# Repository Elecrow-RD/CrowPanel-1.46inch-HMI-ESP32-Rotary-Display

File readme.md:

### 1, Product picture

### 2, Product version number

|      | Hardware | Software | Remark |
| ---- | -------- | -------- | ------ |
| 1    | V1.0     | V1.0     | latest |

### 3, product information

#### Display Module Specifications
| Main Chip: ESP32-S3R8  |                                                              |
| ---------------------- | ------------------------------------------------------------ |
| Processor              | Equipped with high-performance Xtensa 32-bit LX7 dual-core processor, with a main frequency of up to 240MHz |
| System memory          | 512KB SRAM、8M PSRAM                                         |
| Storage                | 16M Flash                                                    |
| Screen                 |                                                              |
| Size                   | 1.46 inch                                                    |
| Screen Type            | IPS                                                          |
| Touch Type             | Capacitive Touch                                             |
| Resolution             | 360*360                                                      |
| Wireless Communication |                                                              |
| Bluetooth              | Bluetooth Low Energy and Bluetooth 5.0                       |
| WiFi                   | Support 802.11a/b/g/n，2.4GH                                 |
| Hardware               |                                                              |
| UART Interface         | 2x UART, ZX-MX 1.25-4P                                       |
| I2C interface          | ZX-MX 1.25-4P                                                |
| FPC connector          | 12P, Power supply burning port, Pitch: 0.5 mm.               |
| Button                 | RESET button, BOOT button, confirmation button (knob press switch) |
| LED Light              | Power indicator, LED ambient light                           |
| Other                  |                                                              |
| Power Input            | 5V/1A                                                        |
| Operating temperature  | -20~65℃                                                      |
| Storage temperature    | -40~80℃                                                      |
| Operation Power        | Module：DC5V  Main Chip：3.3V                                |
| Size                   | 60\*60*27.5mm                                                |
| Shell                  | Plastic + acrylic                                            |
| Net Weight             | 60g                                                          |

### 4, Use the driver module

| Name | dependency library |
| ---- | ------------------ |
| LVGL | lvgl/lvgl@8.3.11   |

### 5,Quick Start

##### Arduino IDE starts

1.Download the library files used by this product to the 'libraries' folder.

C:\Users\Documents\Arduino\libraries\

2.Open the Arduino IDE

3.Open the code configuration environment and burn it.

### 6,Folder structure.

|--3D file： Contains 3D model files (.stp) for the hardware. These files can be used for visualization, enclosure design, or integration into CAD software.

|--Datasheet: Includes datasheets for components used in the project, providing detailed specifications, electrical characteristics, and pin configurations.

|--Eagle_SCH&PCB: Contains **Eagle CAD** schematic (`.sch`) and PCB layout (`.brd`) files. These are used for circuit design and PCB manufacturing.

|--example: Provides example code and projects to demonstrate how to use the hardware and libraries. These examples help users get started quickly.

|--factory_firmware: Stores pre-compiled factory firmware that can be directly flashed onto the device. This ensures the device runs the default functionality.

|--factory_sourcecode: Contains the source code for the factory firmware, allowing users to modify and rebuild the firmware as needed.

### 7,Pin definition

| Function       | GPIO   |
| -------------- | ------ |
| LCD SCLK       | GPIO10 |
| LCD MOSI       | GPIO11 |
| LCD CS         | GPIO9  |
| LCD DC         | GPIO3  |
| LCD RST        | GPIO14 |
| Touch SDA      | GPIO6  |
| Touch SCL      | GPIO7  |
| Touch INT      | GPIO5  |
| Touch RST      | GPIO13 |
| Backlight      | GPIO46 |
| Encoder A      | GPIO45 |
| Encoder B      | GPIO42 |
| Encoder Switch | GPIO41 |
| Power LED      | GPIO40 |
| RGB LED        | GPIO48 |
| I2C_SDA        | GPIO38 |
| I2C_SCL        | GPIO39 |

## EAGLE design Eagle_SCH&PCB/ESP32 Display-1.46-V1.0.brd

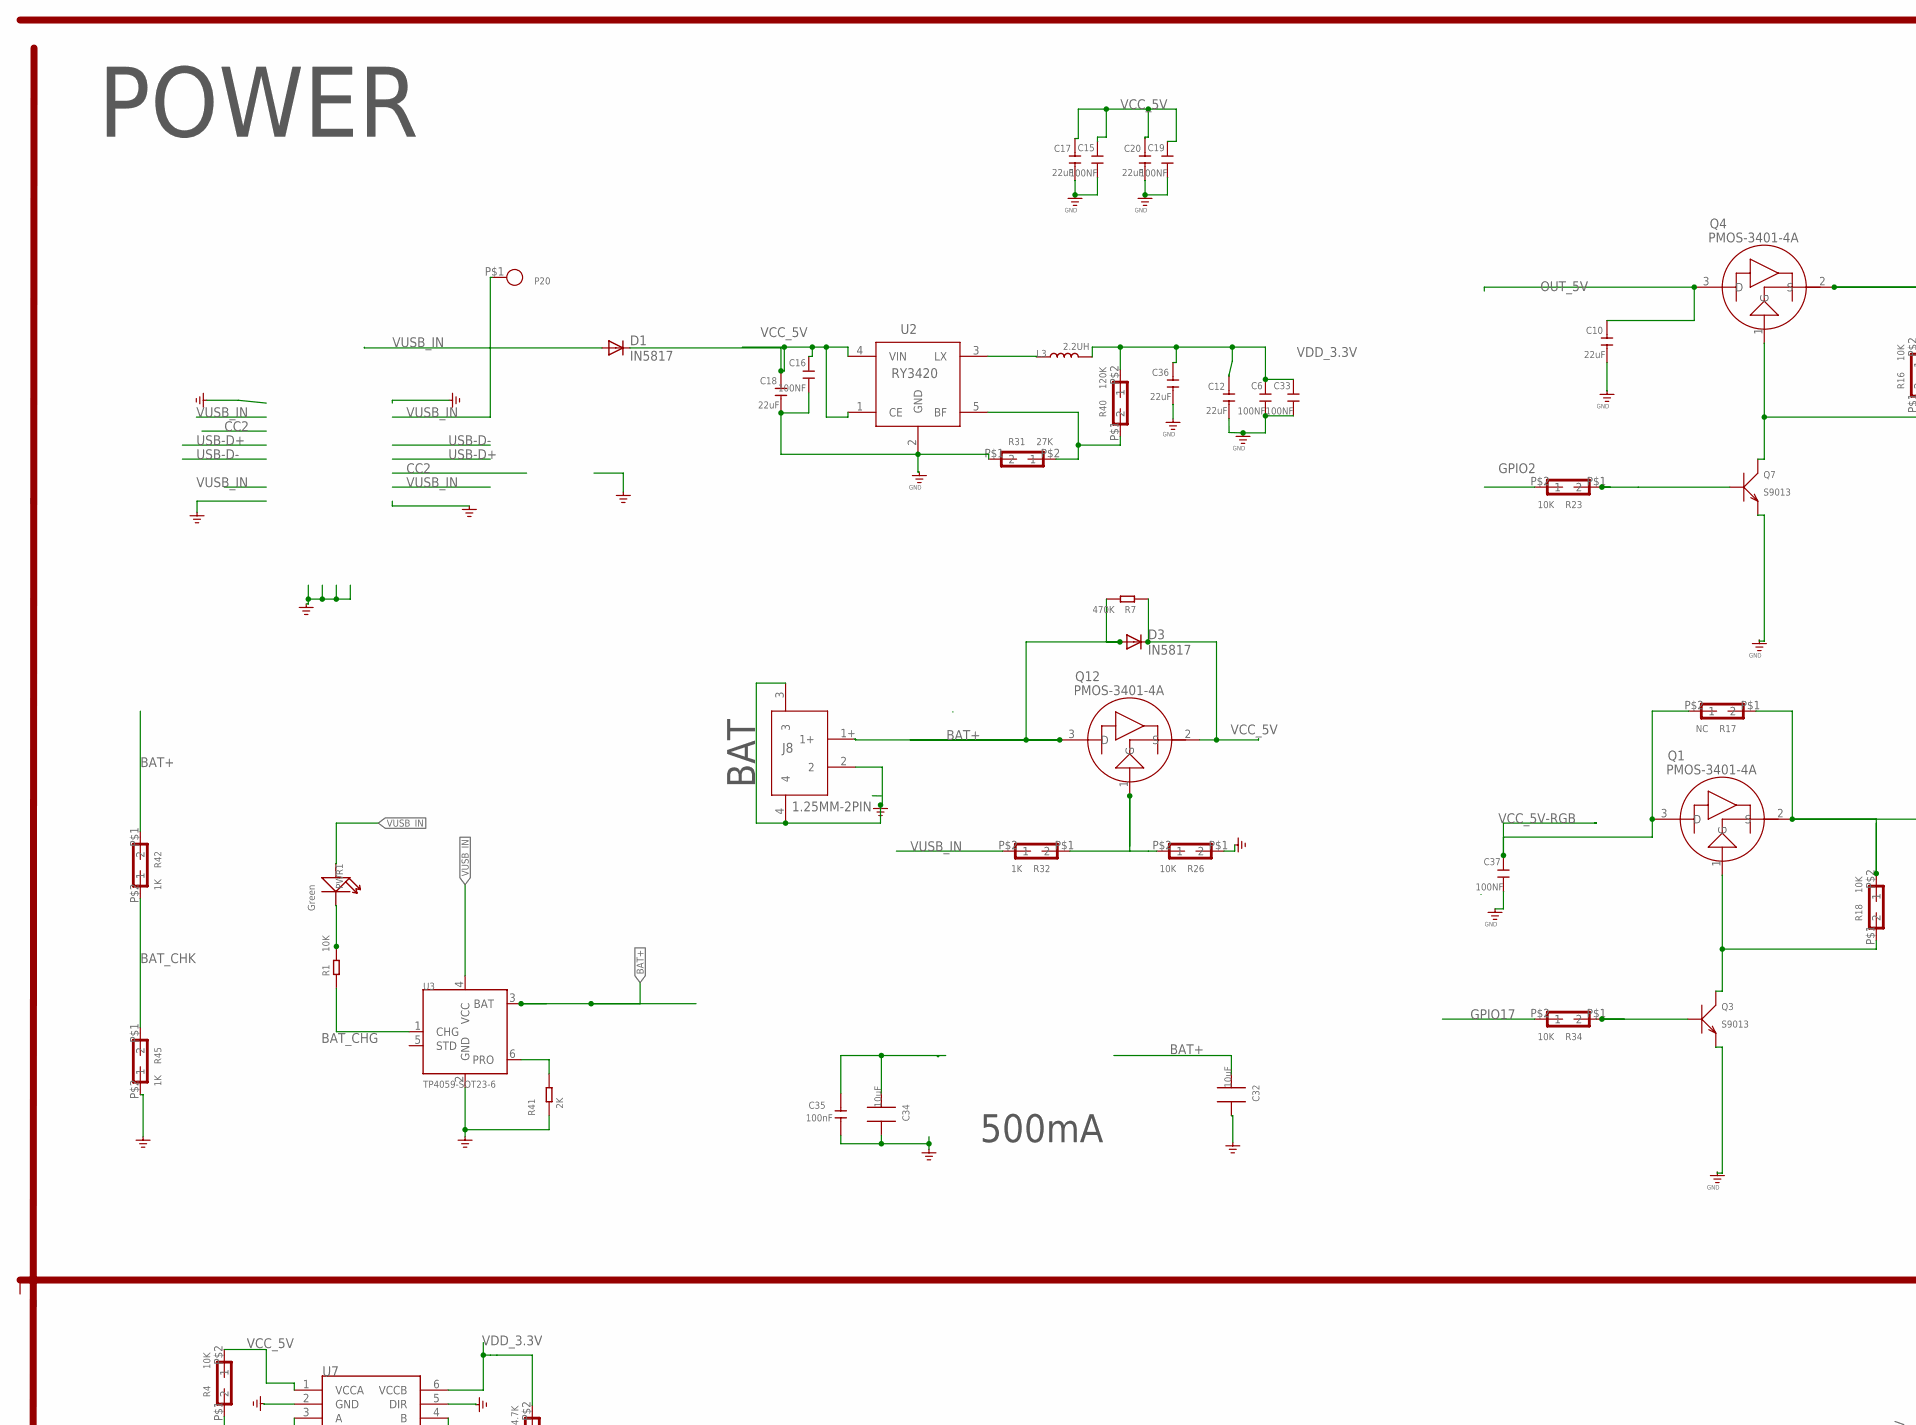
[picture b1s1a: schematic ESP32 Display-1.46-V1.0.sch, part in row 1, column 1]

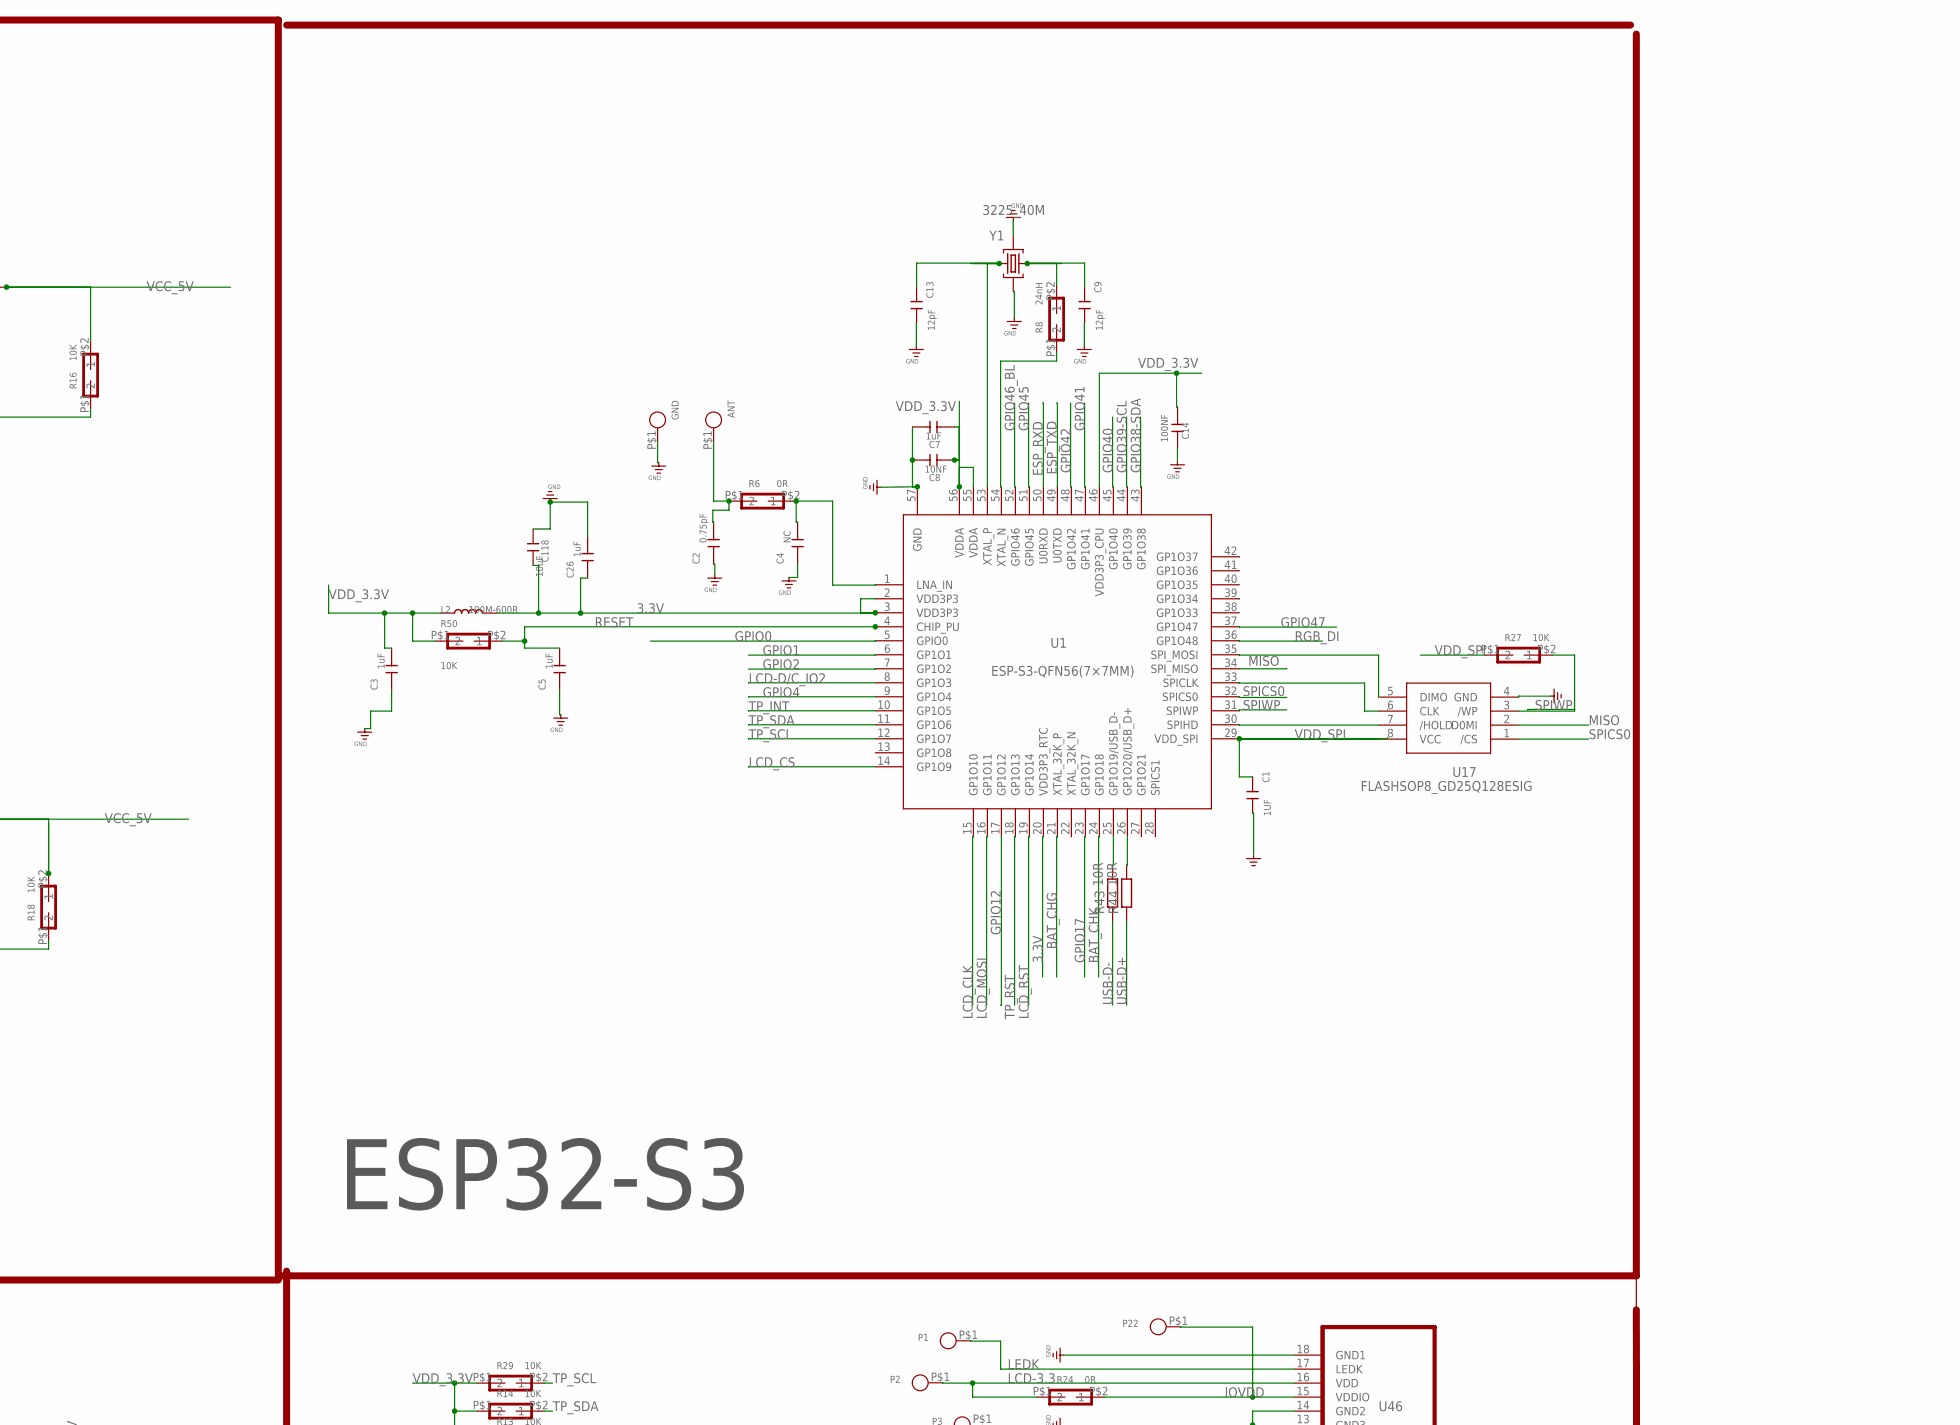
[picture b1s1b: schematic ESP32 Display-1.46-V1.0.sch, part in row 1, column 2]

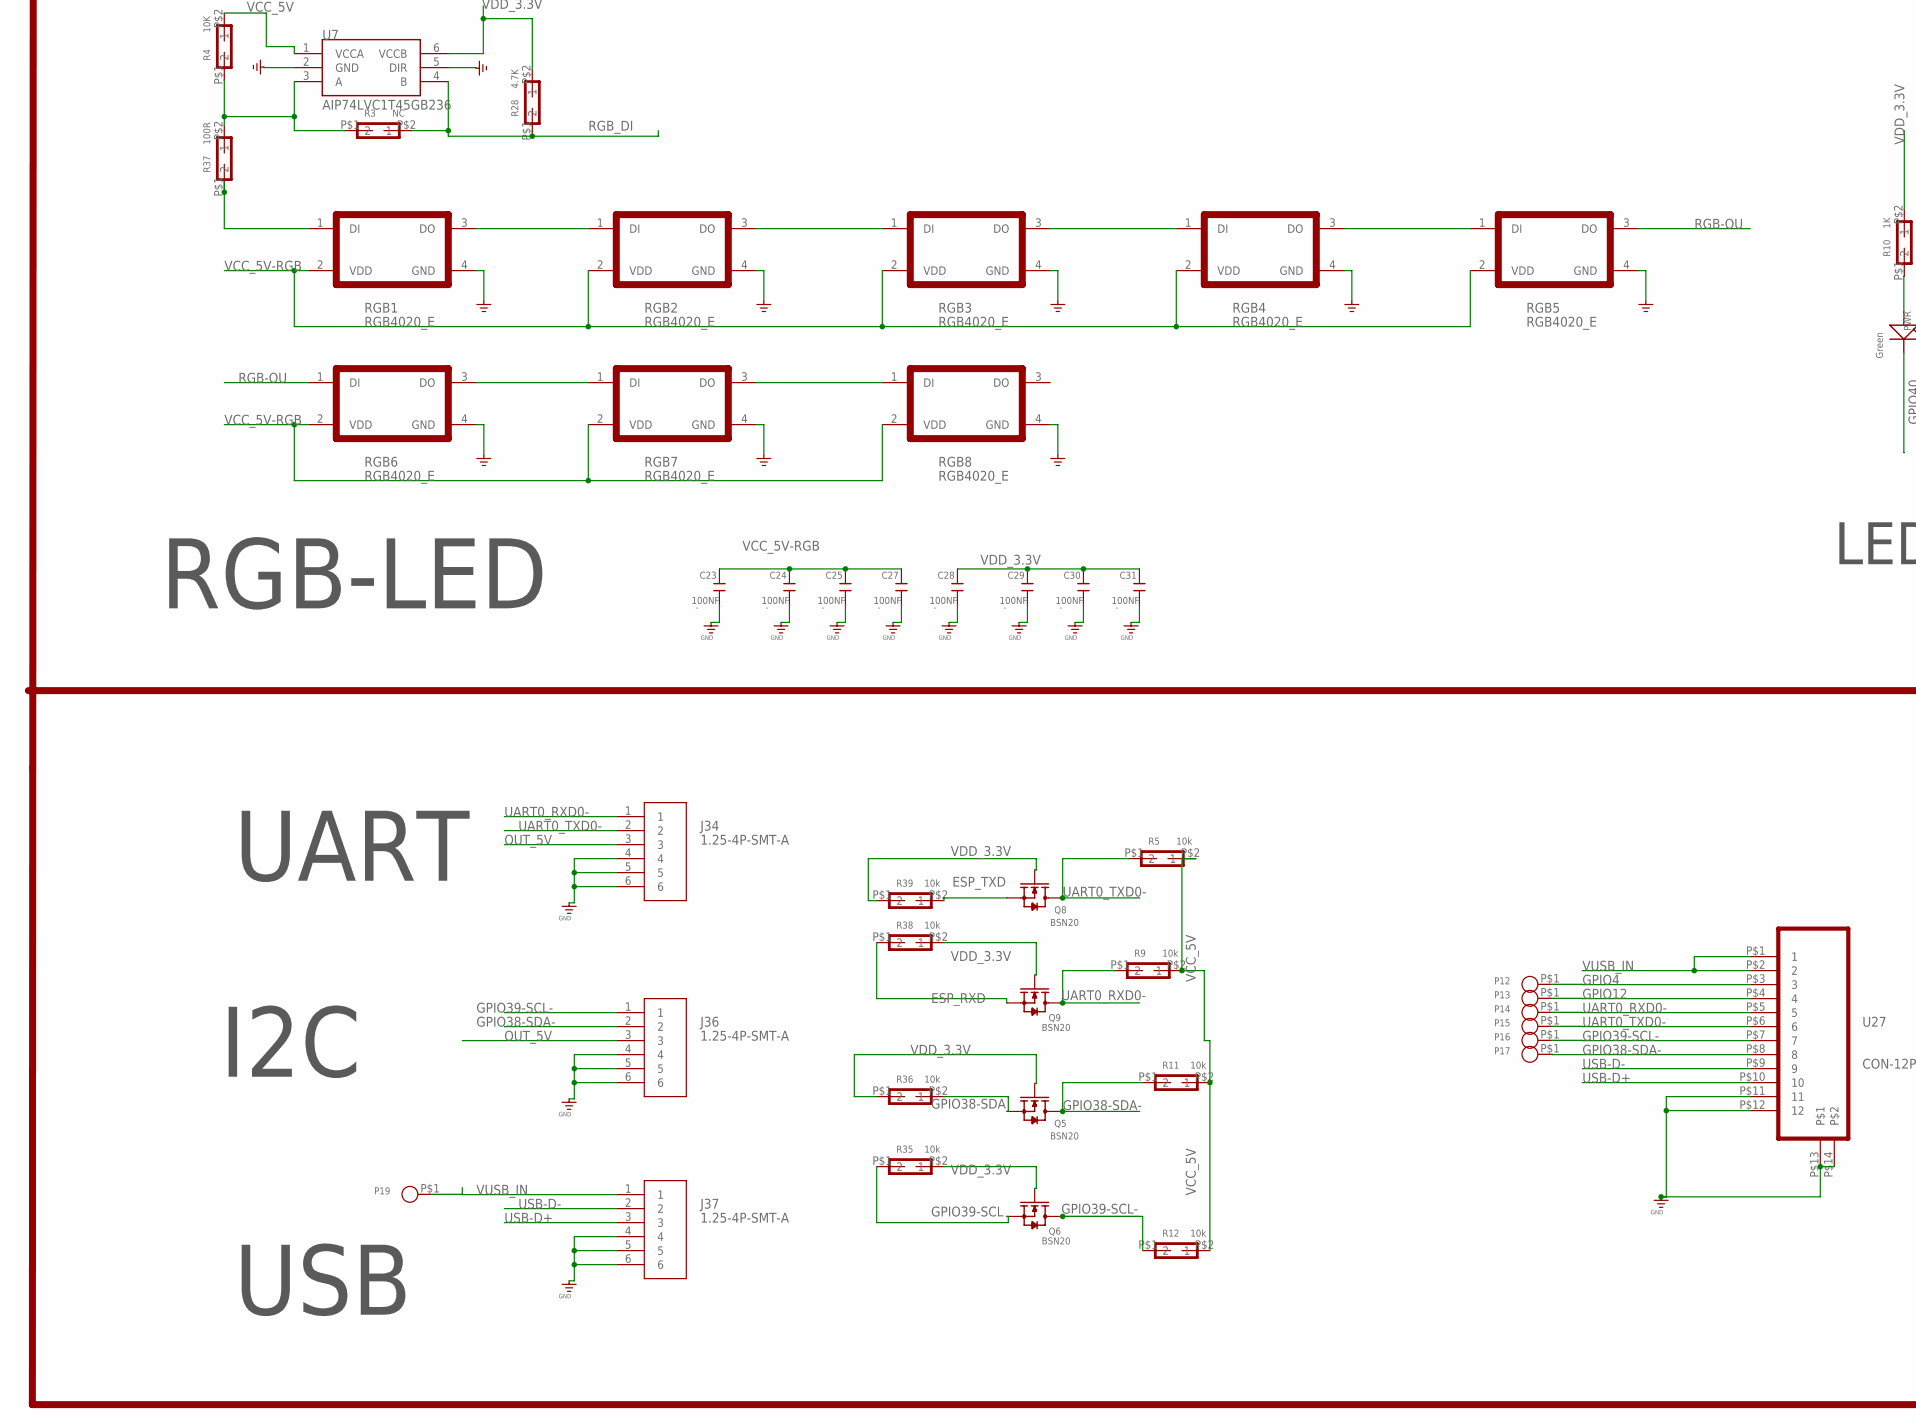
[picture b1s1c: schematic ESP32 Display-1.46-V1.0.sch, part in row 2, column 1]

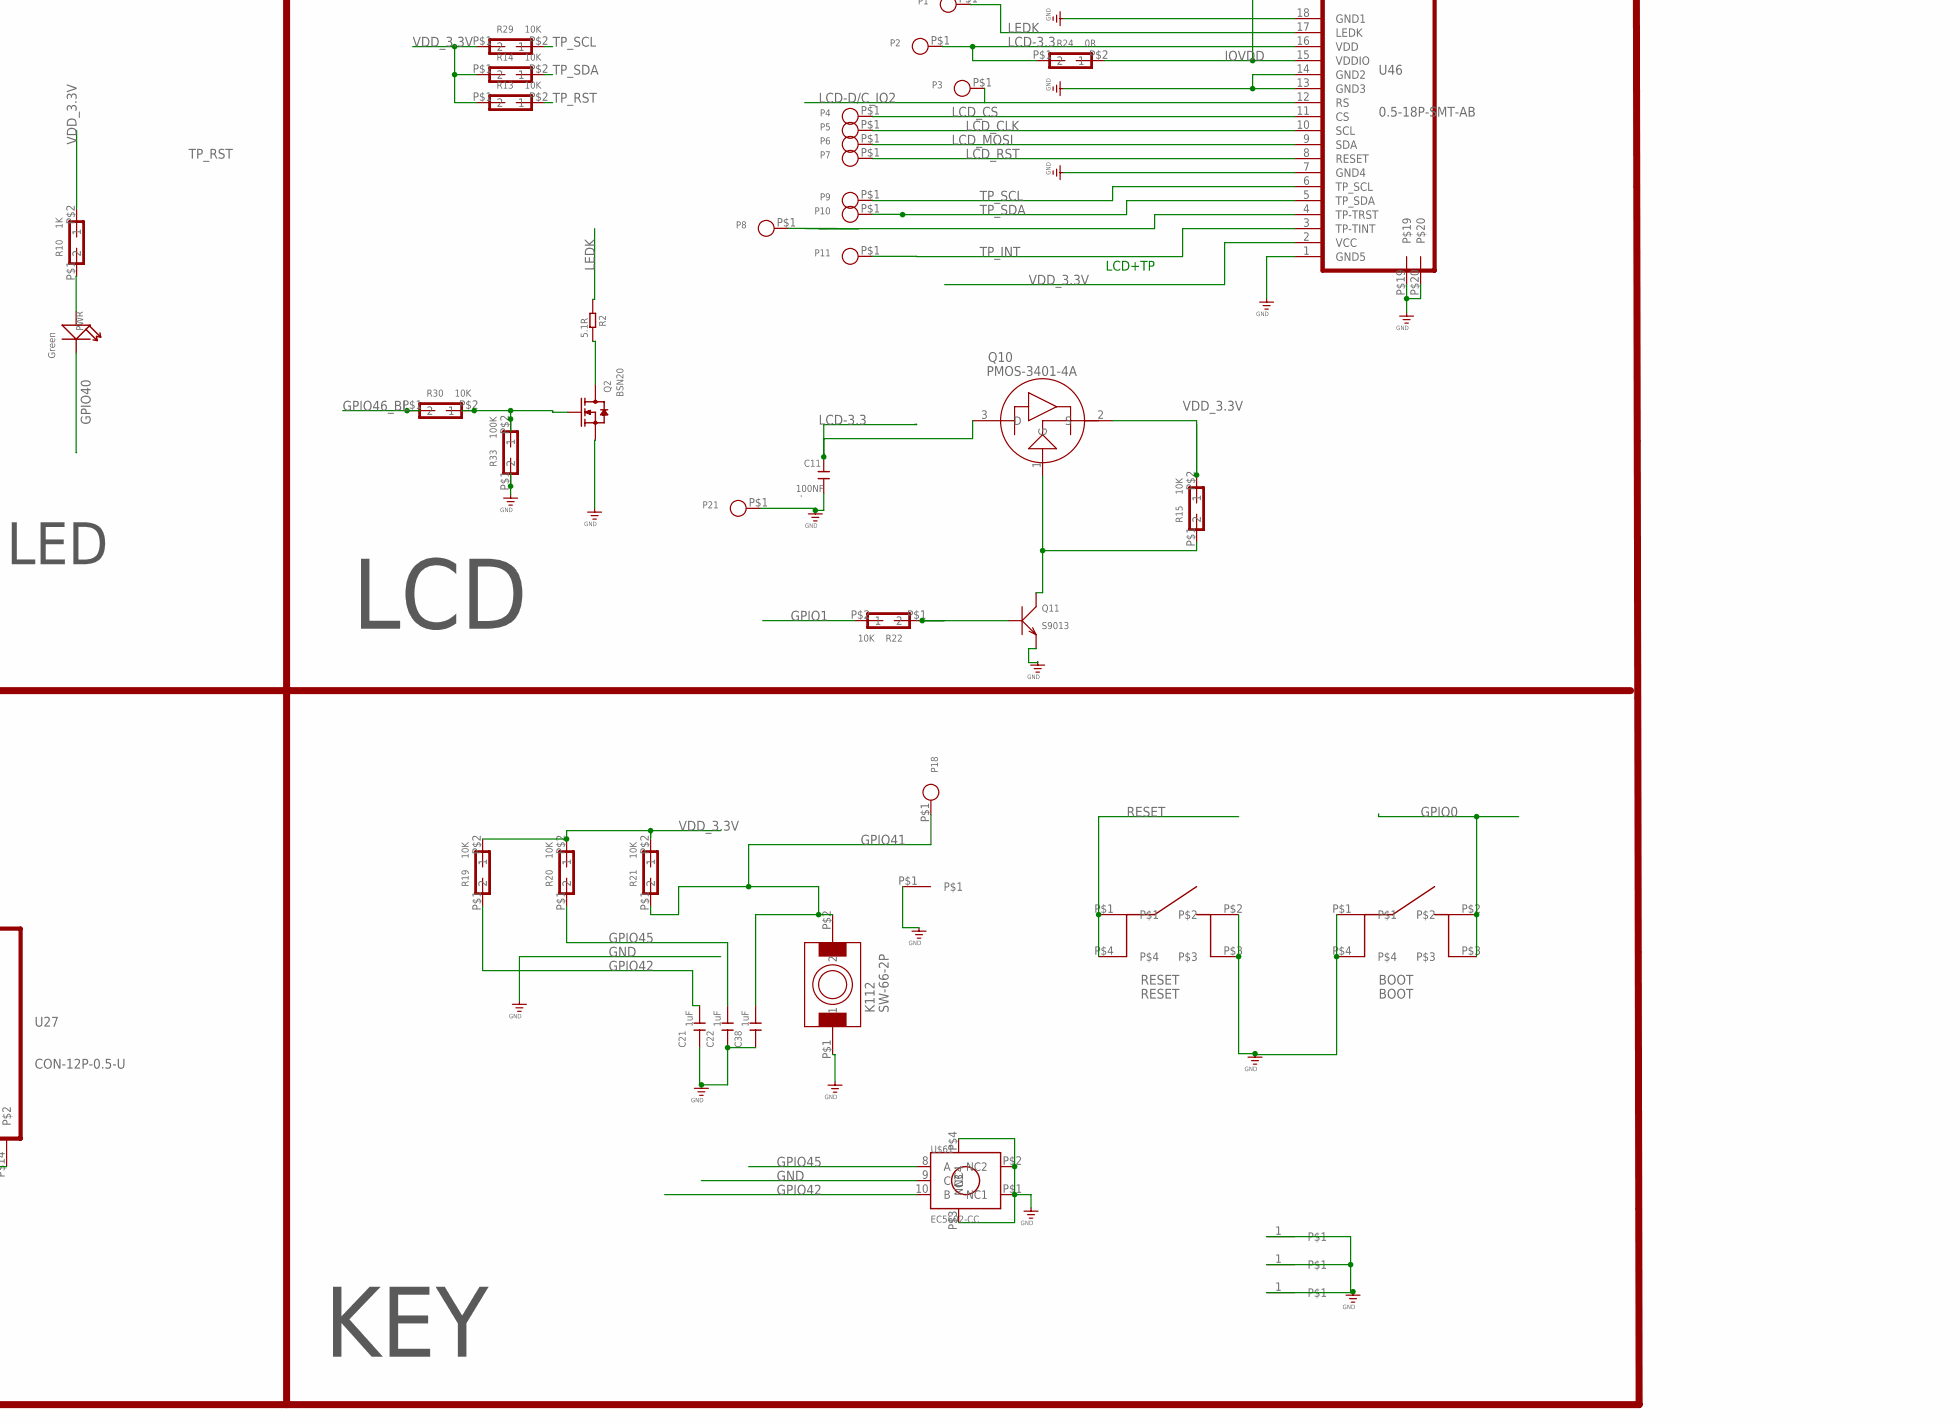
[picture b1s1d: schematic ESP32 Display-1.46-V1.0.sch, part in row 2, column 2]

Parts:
ANT: TEST_PADPAD-1.5MM; TEST_PAD-1.5MM
BOOT: BOOT; SW-4.5*4.5
C1: 1UF; 0402
C2: 0.75pF; C0402
C3, C5, C21, C22, C26, C38: 1uF; C0402
C4: NC; C0402
C6, C11, C15, C16, C19, C23, C24, C25, C27, C28, C29, C30, C31, C33, C37: 100NF; 0603
C7: 1uF; C0603
C8: 10NF; C0603
C9, C13: 12pF; 0402
C10, C12, C17, C18, C20, C36: 22uF; 0805
C14: 100NF; C0603
C32, C34: 10uF; 0805_S
C35: 100nF; C0603
C118: 10uF; 0603
D1, D3: IN5817; DO-214AC
GND: TEST_PADPAD-1.5MM; TEST_PAD-1.5MM
J8: 1.25MM-2PIN; CROWBOT-V1.0库_1.25MM-2PIN
J34, J36, J37: 1.25-4P-SMT-A; 1.25-4P立贴
K112: SW-66-2P; CROWPI_POW_BUTTON_2P
L2: 100M-600R; L0603
L3: 2.2UH; L0420
P1, P2, P3, P4, P5, P6, P7, P8, P9, P10, P11, P12, P13, P14, P15, P16, P17, P18, P19, P20, P21, P22: PADPAD-1.0MM; PAD-1.0MM
PWR, PWR1: Green; LED-0603
Q1, Q4, Q10, Q12: PMOS-3401-4A; SOT-23
Q2, Q5, Q6, Q8, Q9: BSN20; SOT23
Q3, Q7, Q11: S9013; SOT23@1
R1: 10K; R0402
R2: 5.1R; R0603
R3, R17: NC; 0402
R4, R13, R14, R15, R16, R18, R19, R20, R21, R22, R23, R26, R27, R29, R30, R34, R50: 10K; 0402
R5, R9, R11, R12, R35, R36, R38, R39: 10k; 0402
R6, R24: 0R; 0402
R7: 470K; R0402
R8: 24nH; 0402
R10, R32, R42, R45: 1K; 0402
R28: 4.7K; 0402
R31: 27K; 0402
R33: 100K; 0402
R37: 100R; 0402
R40: 120K; 0402
R41: 2K; R0402
R43, R44: 10R; R0402
RESET: RESET; SW-4.5*4.5
RGB1, RGB2, RGB3, RGB4, RGB5, RGB6, RGB7, RGB8: RGB4020_E; RGB4020
T1, T2, T3: T2.5-A; T-2.5
U1: ESP-S3-QFN56(7×7MM)
U2: RY3420; SOT23-5
U3: TP4059-SOT23-6; SOT23-6L
U7: AIP74LVC1T45GB236; SOT23-6L
U17: FLASHSOP8_GD25Q128ESIG; FLASHSOP8_SOP8
U27: CON-12P-0.5-U; CON-0.5-12P-U
U46: 0.5-18P-SMT-AB; 0.5MM-18P
U$61: EC5602-CC
U$64: T-2-1.1
Y1: 3225_40M; CRYSTAL-3.2-2.5

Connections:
3.3V: C26.1, C118.2, L2.2, U1.2 (VDD3P3), U1.3 (VDD3P3), U1.20 (VDD3P3_RTC)
BAT+: C32.2, D3.A, J8.1+, Q12.3 (D), R7.1, R42.P$1 (1), U3.3 (BAT)
BAT_CHG: R1.2, U1.21 (XTAL_32K_P), U3.1 (CHG)
BAT_CHK: R42.P$2 (2), R45.P$1 (1), U1.24 (GP1O18)
ESP_RXD: Q9.2 (S), R38.P$1 (1), U1.50 (U0RXD)
ESP_TXD: Q8.2 (S), R39.P$2 (2), U1.49 (U0TXD)
GND: BOOT.P$1, BOOT.P$4, C1.2, C2.1, C3.1, C4.1, C5.1, C6.2, C7.2, C8.2, C9.2, C10.1, C11.2, C12.1, C13.2, C14.2, C15.2, C16.2, C17.1, C18.1, C19.2, C20.1, C21.1, C22.1, C23.2, C24.2, C25.2, C26.2, C27.2, C28.2, C29.2, C30.2, C31.2, C32.1, C33.2, C34.1, C35.2, C36.1, C37.2, C38.1, C118.1, GND.P$1, J8.2, J8.3, J8.4, J34.4, J34.5, J34.6, J36.4, J36.5, J36.6, J37.4, J37.5, J37.6, K112.P$1 (1), P21.P$1, Q2.2 (S), Q3.2 (E), Q7.2 (E), Q11.2 (E), R26.P$1 (1), R31.P$1 (1), R33.P$1 (1), R41.1, R45.P$2 (2), RESET.P$2, RESET.P$3, RGB1.4 (GND), RGB2.4 (GND), RGB3.4 (GND), RGB4.4 (GND), RGB5.4 (GND), RGB6.4 (GND), RGB7.4 (GND), RGB8.4 (GND), T1.1, T2.1, T3.1, U1.57 (GND), U2.2 (GND), U3.2 (GND), U7.2 (GND), U7.5 (DIR), U17.4 (GND), U27.P$11 (11), U27.P$12 (12), U27.P$13, U27.P$14, U46.1 (GND5), U46.7 (GND4), U46.13 (GND3), U46.14 (GND2), U46.18 (GND1), U46.P$19, U46.P$20, U$61.9 (C), U$61.P$1 (NC1), U$61.P$2 (NC2), U$61.P$3 (NC3), U$61.P$4 (NC4), U$64.P$1, Y1.2 (GND), Y1.4 (GND)
GPIO0: BOOT.P$2, BOOT.P$3, U1.5 (GPIO0)
GPIO1: R22.P$2 (2), U1.6 (GP1O1)
GPIO2: R23.P$2 (2), U1.7 (GP1O2)
GPIO4: P12.P$1, U1.9 (GP1O4), U27.P$3 (3)
GPIO12: P13.P$1, U1.17 (GP1O12), U27.P$4 (4)
GPIO17: R34.P$2 (2), U1.23 (GP1O17)
GPIO34: U1.39 (GP1O34)
GPIO37: U1.42 (GP1O37)
GPIO38-SDA: Q5.2 (S), R36.P$2 (2), U1.43 (GP1O38)
GPIO38-SDA-: J36.2, P17.P$1, Q5.3 (D), R11.P$1 (1), U27.P$8 (8)
GPIO39-SCL: Q6.2 (S), R35.P$1 (1), U1.44 (GP1O39)
GPIO39-SCL-: J36.1, P16.P$1, Q6.3 (D), R12.P$1 (1), U27.P$7 (7)
GPIO40: PWR.-, U1.45 (GP1O40)
GPIO41: C38.2, K112.P$2 (2), P18.P$1, R21.P$1 (1), U1.47 (GP1O41)
GPIO42: C21.2, R19.P$1 (1), U1.48 (GP1O42), U$61.10 (B)
GPIO45: C22.2, R20.P$1 (1), U1.51 (GPIO45), U$61.8 (A)
GPIO46_BL: R30.P$1 (1), U1.52 (GPIO46)
GPIO47: U1.37 (GP1O47)
IOVDD: P22.P$1, R24.P$2 (2), U46.15 (VDDIO)
LCD-3.3: C11.1, P2.P$1, Q10.3 (D), R24.P$1 (1), U46.16 (VDD)
LCD-D/C_IO2: P3.P$1, U1.8 (GP1O3), U46.12 (RS)
LCD_CLK: P5.P$1, U1.15 (GP1O10), U46.10 (SCL)
LCD_CS: P4.P$1, U1.14 (GP1O9), U46.11 (CS)
LCD_MOSI: P6.P$1, U1.16 (GP1O11), U46.9 (SDA)
LCD_RST: P7.P$1, U1.19 (GP1O14), U46.8 (RESET)
LEDK: P1.P$1, R2.2, U46.17 (LEDK)
MISO: U1.34 (SPI_MISO), U17.2 (D0MI)
unnamed: Q4.1 (G), Q7.3 (C), R16.P$1 (1)
unnamed: RGB1.3 (DO), RGB2.1 (DI)
unnamed: L3.1, U2.3 (LX)
unnamed: RGB2.3 (DO), RGB3.1 (DI)
unnamed: PWR.+, R10.P$1 (1)
unnamed: ANT.P$1, C2.2, R6.P$1 (1)
unnamed: RGB3.3 (DO), RGB4.1 (DI)
unnamed: R43.2, U1.25 (GP1O19/USB_D-)
unnamed: R41.2, U3.6 (PRO)
unnamed: Q12.1 (G), R26.P$2 (2), R32.P$1 (1)
unnamed: Q2.3 (D), R2.1
unnamed: R31.P$2 (2), R40.P$1 (1), U2.5 (BF)
unnamed: Q2.1 (G), R30.P$2 (2), R33.P$2 (2)
unnamed: R44.2, U1.26 (GP1O20/USB_D+)
unnamed: R3.P$1 (1), R4.P$1 (1), R37.P$2 (2), U7.3 (A)
unnamed: R37.P$1 (1), RGB1.1 (DI)
unnamed: U1.35 (SPI_MOSI), U17.5 (DIMO)
unnamed: U1.33 (SPICLK), U17.6 (CLK)
unnamed: RGB4.3 (DO), RGB5.1 (DI)
unnamed: U1.30 (SPIHD), U17.7 (/HOLD)
unnamed: Q10.1 (G), Q11.3 (C), R15.P$1 (1)
unnamed: Q11.1 (B), R22.P$1 (1)
unnamed: Q7.1 (B), R23.P$1 (1)
unnamed: RGB6.3 (DO), RGB7.1 (DI)
unnamed: RGB7.3 (DO), RGB8.1 (DI)
unnamed: Q1.1 (G), Q3.3 (C), R18.P$1 (1)
unnamed: Q3.1 (B), R34.P$1 (1)
unnamed: PWR1.-, R1.1
unnamed: C9.1, R8.P$2 (2), Y1.1 (C1)
unnamed: R8.P$1 (1), U1.54 (XTAL_N)
unnamed: C4.2, R6.P$2 (2), U1.1 (LNA_IN)
unnamed: C13.1, U1.53 (XTAL_P), Y1.3 (C2)
OUT_5V: C10.2, J34.3, J36.3, Q4.3 (D)
RESET: C5.2, R50.P$2 (2), RESET.P$1, RESET.P$4, U1.4 (CHIP_PU)
RGB-OU: RGB5.3 (DO), RGB6.1 (DI)
RGB_DI: R3.P$2 (2), R28.P$1 (1), U1.36 (GP1O48), U7.4 (B)
SPICS0: U1.32 (SPICS0), U17.1 (/CS)
SPIWP: R27.P$2 (2), U1.31 (SPIWP), U17.3 (/WP)
TP_INT: P11.P$1, U1.10 (GP1O5), U46.3 (TP-TINT)
TP_RST: P8.P$1, R13.P$2 (2), U1.18 (GP1O13), U46.4 (TP-TRST)
TP_SCL: P9.P$1, R29.P$2 (2), U1.12 (GP1O7), U46.6 (TP_SCL)
TP_SDA: P10.P$1, R14.P$2 (2), U1.11 (GP1O6), U46.5 (TP_SDA)
UART0_RXD0-: J34.1, P14.P$1, Q9.3 (D), R9.P$1 (1), U27.P$5 (5)
UART0_TXD0-: J34.2, P15.P$1, Q8.3 (D), R5.P$1 (1), U27.P$6 (6)
USB-D+: J37.3, R44.1, U27.P$10 (10)
USB-D-: J37.2, R43.1, U27.P$9 (9)
VCC_5V: C15.1, C16.1, C17.2, C18.2, C19.1, C20.2, D1.C, D3.C, Q1.2 (S), Q4.2 (S), Q12.2 (S), R4.P$2 (2), R5.P$2 (2), R7.2, R9.P$2 (2), R11.P$2 (2), R12.P$2 (2), R16.P$2 (2), R17.P$1 (1), R18.P$2 (2), U2.1 (CE), U2.4 (VIN), U7.1 (VCCA)
VCC_5V-RGB: C23.1, C24.1, C25.1, C27.1, C37.1, Q1.3 (D), R17.P$2 (2), RGB1.2 (VDD), RGB2.2 (VDD), RGB3.2 (VDD), RGB4.2 (VDD), RGB5.2 (VDD), RGB6.2 (VDD), RGB7.2 (VDD), RGB8.2 (VDD)
VDD_3.3V: C3.2, C6.1, C7.1, C8.1, C12.2, C14.1, C28.1, C29.1, C30.1, C31.1, C33.1, C36.2, L2.1, L3.2, Q5.1 (G), Q6.1 (G), Q8.1 (G), Q9.1 (G), Q10.2 (S), R10.P$2 (2), R13.P$1 (1), R14.P$1 (1), R15.P$2 (2), R19.P$2 (2), R20.P$2 (2), R21.P$2 (2), R28.P$2 (2), R29.P$1 (1), R35.P$2 (2), R36.P$1 (1), R38.P$2 (2), R39.P$1 (1), R40.P$2 (2), R50.P$1 (1), U1.46 (VDD3P3_CPU), U1.55 (VDDA), U1.56 (VDDA), U7.6 (VCCB), U46.2 (VCC)
VDD_SPI: C1.1, R27.P$1 (1), U1.29 (VDD_SPI), U17.8 (VCC)
VUSB_IN: C34.2, C35.1, D1.A, J37.1, P19.P$1, P20.P$1, PWR1.+, R32.P$2 (2), U3.4 (VCC), U27.P$1 (1), U27.P$2 (2)

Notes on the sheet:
LED
RGB-LED
ESP32-S3
LCD+TP
UART
I2C
USB
LCD
POWER
KEY
BAT
500mA

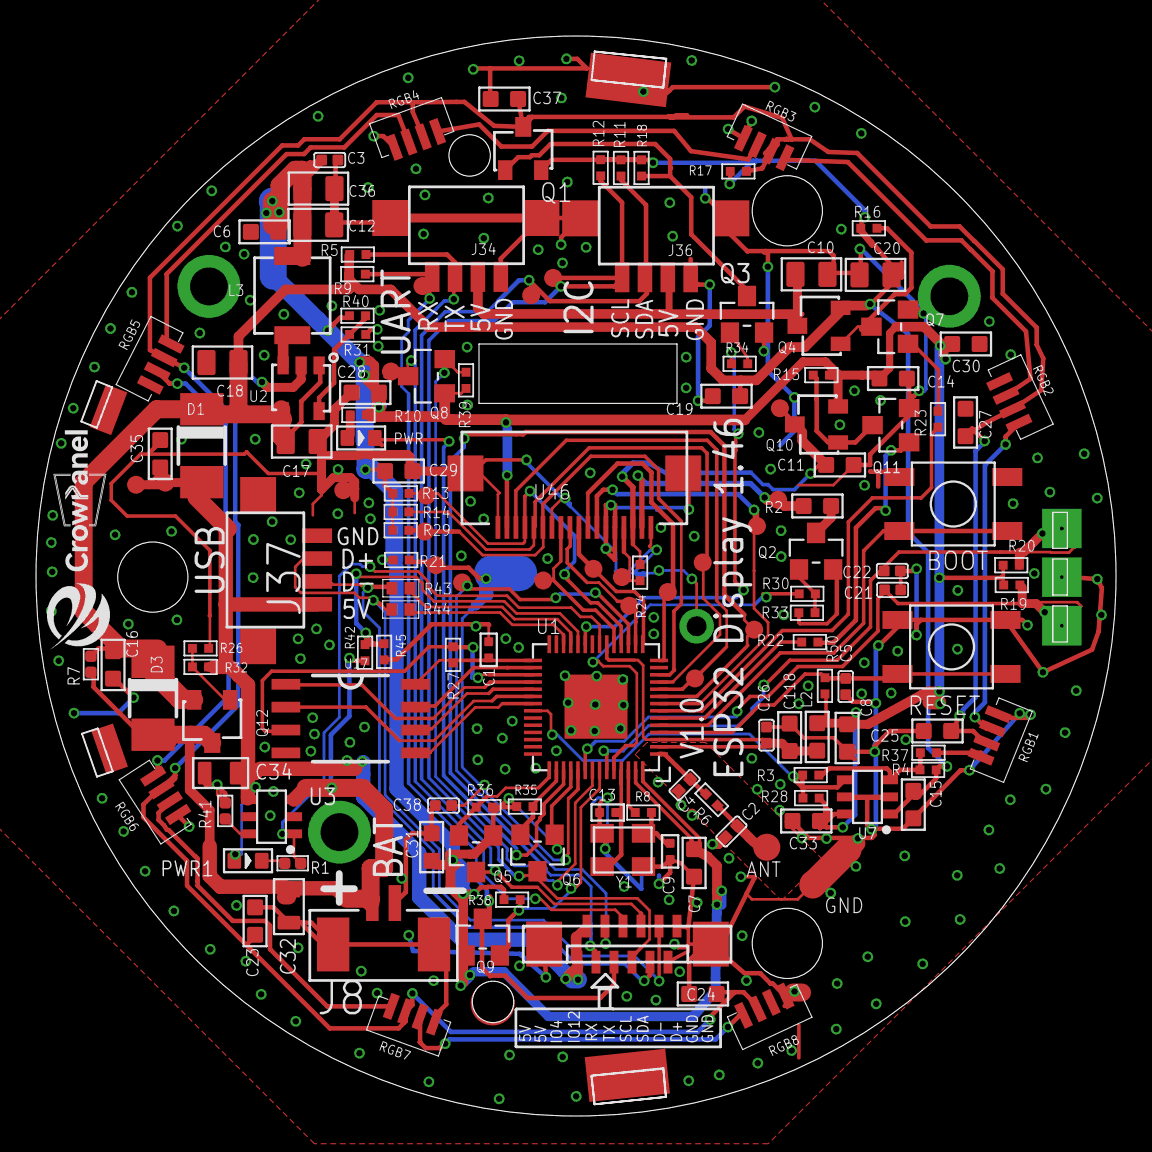
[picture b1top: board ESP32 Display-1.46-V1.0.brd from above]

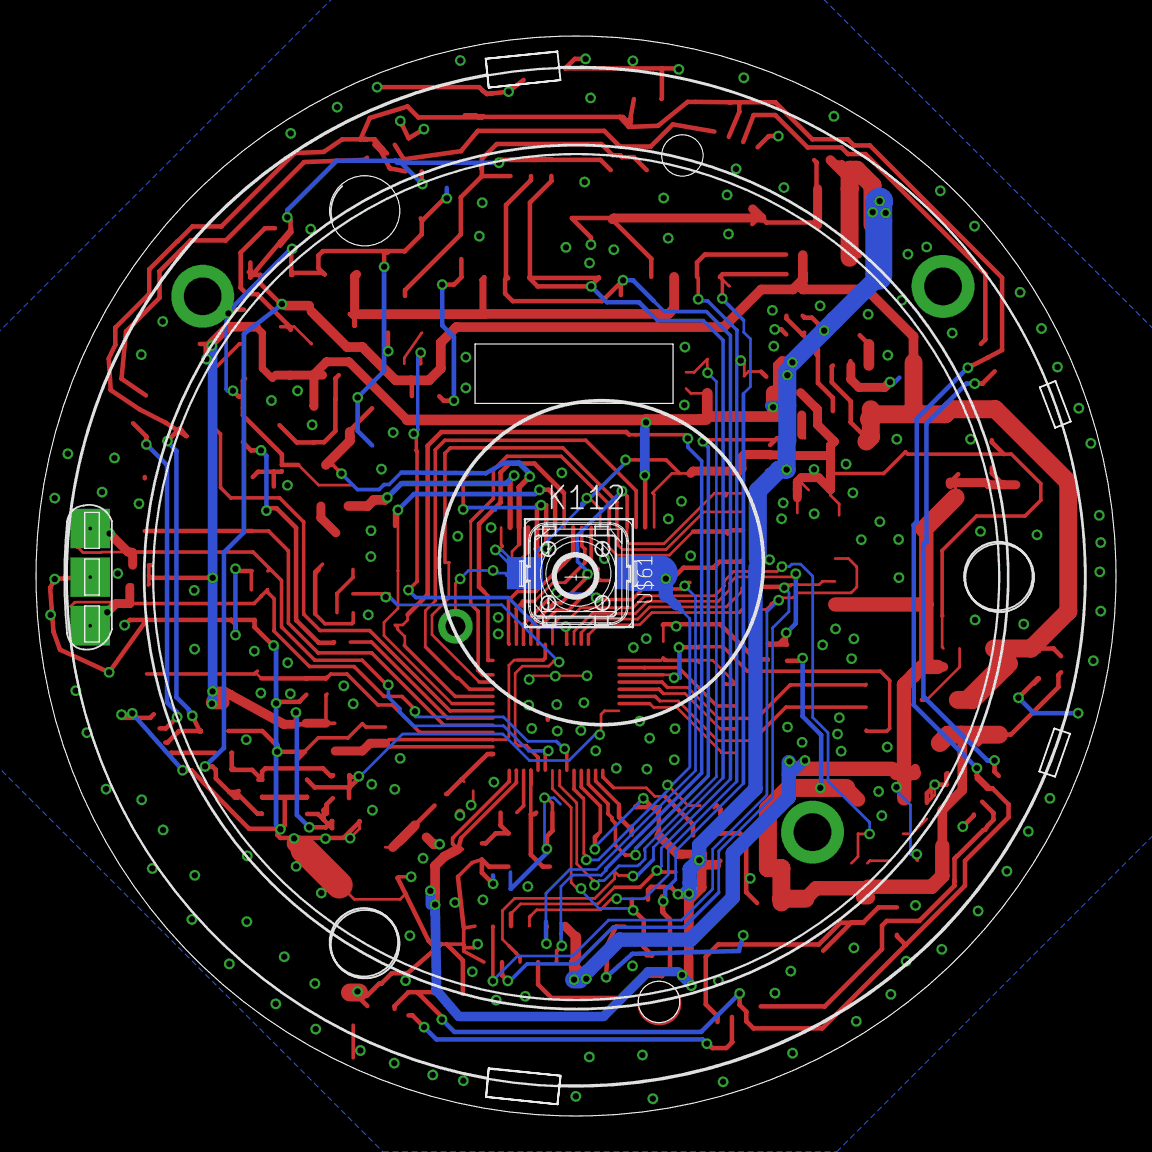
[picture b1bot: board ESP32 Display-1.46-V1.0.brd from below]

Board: 2 copper layers, 60.0 x 60.0 mm, 156 parts (2 on the bottom side), 82 nets.

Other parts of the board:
U$9: LOGO-1.46
U$51: LOGO公司图标
